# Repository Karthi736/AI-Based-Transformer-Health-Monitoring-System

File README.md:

# Industrial Transformer Health Monitoring SCADA System

<div align="center">

</div>

---

---

An ESP32-based transformer health monitoring and preventive protection system with Firebase cloud communication and an industrial SCADA web dashboard.

## Project Overview

Transformer health monitoring is important for identifying abnormal operating conditions before they develop into serious faults.

This project demonstrates a smart monitoring and preventive protection approach using ESP32, DHT22, load simulation, relay protection, servo-based cooling, local LCD monitoring, Firebase cloud communication, and an industrial SCADA web dashboard.

The system continuously monitors transformer-related parameters and converts the collected information into an easy-to-understand health and risk status.

The overall monitoring workflow is:

**Sensors → ESP32 → Health Assessment → Risk Classification → Preventive Protection → Firebase → SCADA Dashboard**

---

## Key Features

- Real-time transformer condition monitoring
- Temperature monitoring
- Humidity monitoring
- Load percentage monitoring
- Transformer health score calculation
- LOW, MEDIUM, HIGH, and CRITICAL risk classification
- Automatic preventive protection
- Relay-based protection control
- Servo-based cooling control
- LED warning indication
- Buzzer alarm indication
- 16×2 I2C LCD monitoring
- ESP32-based processing
- Wi-Fi communication
- Firebase cloud communication
- Industrial SCADA web dashboard
- Remote transformer status monitoring
- Multi-transformer monitoring
- Separate simulation units for TR-001, TR-002, TR-003, and TR-004

---

## System Architecture

The complete system follows the architecture:

**DHT22 + Load Input → ESP32 → Health Assessment → Risk Classification → Preventive Protection → Firebase → SCADA Dashboard**

---

## Documentation

### System Architecture

<div align="center">

</div>

### Block Diagram

<div align="center">

</div>

### Flowchart

<div align="center">

</div>

### Circuit Diagram

<div align="center">

</div>

---

## Hardware Components

| Component | Function |
|---|---|
| ESP32 | Main controller, data processing, Wi-Fi and Firebase communication |
| DHT22 | Temperature and humidity monitoring |
| Potentiometer | Transformer load percentage simulation |
| 16×2 I2C LCD | Local transformer monitoring and status display |
| Relay Module | Preventive protection control |
| Servo Motor | Automatic cooling mechanism |
| LED | Visual warning indication |
| Buzzer | Audible alarm indication |

---

## Hardware Functions

### ESP32

The ESP32 acts as the central controller of the system. It collects sensor values, processes transformer operating parameters, calculates the health score, determines the risk level, controls protection devices, and communicates monitoring data to Firebase through Wi-Fi.

### DHT22

The DHT22 sensor provides temperature and humidity measurements used for transformer condition monitoring.

### Potentiometer

The potentiometer is used as a simulated load input. Its value represents the transformer load percentage during the simulation.

### 16×2 I2C LCD

The LCD provides local monitoring of important transformer parameters and operating status.

### Relay Module

The relay provides a control mechanism for preventive protection during critical transformer conditions.

### Servo Motor

The servo motor represents an automatic cooling mechanism that operates according to the transformer risk condition.

### LED

The LED provides a visual warning indication when abnormal or critical conditions are detected.

### Buzzer

The buzzer provides an audible alarm during abnormal and critical operating conditions.

---

## Technologies Used

- ESP32
- Arduino IDE
- DHT22
- 16×2 I2C LCD
- Potentiometer
- Relay Module
- Servo Motor
- LED
- Buzzer
- Wi-Fi
- Firebase
- HTML
- CSS
- JavaScript
- SCADA Web Dashboard
- Wokwi Simulation

---

## Monitoring Parameters

The system monitors the following parameters:

| Parameter | Source | Purpose |
|---|---|---|
| Temperature | DHT22 | Transformer thermal condition |
| Humidity | DHT22 | Environmental monitoring |
| Load Percentage | Potentiometer | Transformer load simulation |
| Health Score | ESP32 | Overall transformer condition |
| Risk Level | ESP32 | Transformer condition classification |
| Relay Status | ESP32 | Preventive protection status |
| Cooling Status | Servo | Cooling mechanism status |
| Alarm Status | LED + Buzzer | Warning and critical indication |
| Fault Count | ESP32 | Critical fault tracking |
| Transformer Status | ESP32 / Firebase | Overall operating condition |

---

## Health and Risk Classification

The transformer condition is classified using the calculated health score.

| Health Score | Risk Level | System Response |
|---|---|---|
| 80–100 | LOW | Normal Monitoring |
| 50–79 | MEDIUM | Warning Monitoring |
| 25–49 | HIGH | Preventive Action |
| Below 25 | CRITICAL | Protection Activated |

The health score provides a simplified representation of the transformer operating condition and allows the system to classify the current risk level.

---

## Preventive Protection

The system is designed to respond automatically when a critical transformer condition is detected.

During a critical condition:

- Relay protection is activated.
- Servo-based cooling is activated.
- LED warning indication is enabled.
- Buzzer alarm is activated.
- LCD status is updated.
- Transformer status is updated in Firebase.
- SCADA dashboard displays the updated protection condition.

This provides an automated preventive response instead of relying only on manual monitoring.

---

## Firebase Cloud Communication

The ESP32 communicates with Firebase using Wi-Fi.

Firebase acts as the cloud data layer between the ESP32 monitoring system and the SCADA web dashboard.

The monitoring data transmitted to Firebase can include:

- Temperature
- Humidity
- Load Percentage
- Health Score
- Risk Level
- Relay Status
- Cooling Status
- Alarm Status
- Fault Count
- Transformer Status

The SCADA dashboard uses the Firebase data to provide centralized remote monitoring.

---

## SCADA Web Dashboard

The industrial SCADA web dashboard provides a centralized interface for monitoring transformer operating conditions.

The dashboard can display:

- Real-time Temperature
- Humidity
- Load Percentage
- Health Score
- Risk Level
- Relay Status
- Cooling Status
- Alarm Status
- Fault Count
- Transformer Status

The dashboard is designed to provide a clear view of transformer health and protection status.

The multi-transformer configuration allows separate transformer units to be monitored from a centralized SCADA interface.

---

## Multi-Transformer Simulation

The project includes four separate transformer simulation units.

### TR-001

[View TR-001 Wokwi Simulation](https://wokwi.com/projects/472072364712871937)

### TR-002

[View TR-002 Wokwi Simulation](https://wokwi.com/projects/471997864432481281)

### TR-003

[View TR-003 Wokwi Simulation](https://wokwi.com/projects/471997923499829249)

### TR-004

[View TR-004 Wokwi Simulation](https://wokwi.com/projects/471997982880700417)

These simulation units demonstrate the monitoring concept for multiple transformer units.

---

## Simulation Conditions

The system can be evaluated under different operating conditions by changing the temperature and load inputs.

### Normal Condition

Under normal operating conditions:

- Health score remains high.
- Risk level remains LOW.
- Relay protection remains inactive.
- Cooling remains inactive.
- Alarm indication remains OFF.
- Transformer status remains normal.

### Warning Condition

When temperature or load increases:

- Health score decreases.
- Risk level changes to MEDIUM or HIGH depending on the calculated condition.
- Warning indication is generated.
- LCD displays the updated condition.
- Monitoring information is updated in the cloud dashboard.

### Critical Condition

When the transformer operating condition reaches a critical level:

- Risk level becomes CRITICAL.
- Relay protection is activated.
- Servo cooling is activated.
- LED warning is activated.
- Buzzer alarm is activated.
- Firebase data is updated.
- SCADA dashboard displays the critical transformer condition.
---
## Advantages

- Continuous transformer condition monitoring
- Real-time temperature and humidity monitoring
- Load condition monitoring
- Automatic transformer health assessment
- Automatic risk classification
- Preventive protection response
- Automatic cooling control
- Local LCD monitoring
- LED and buzzer warning indication
- Firebase cloud communication
- Remote SCADA monitoring
- Centralized multi-transformer monitoring
- Real-time transformer status visualization
- Expandable monitoring architecture
- Suitable as a prototype for smart transformer monitoring applications

---

## Future Scope

The system can be further developed by integrating additional transformer parameters and advanced monitoring technologies.

- Transformer oil temperature monitoring
- Transformer oil level monitoring
- Transformer current and voltage monitoring
- Transformer vibration monitoring
- Power factor monitoring
- Energy monitoring
- Historical transformer data analysis
- Real-time trend analysis
- Advanced predictive maintenance algorithms
- Machine learning-based fault prediction
- Automated fault classification
- Mobile monitoring application
- Large-scale multi-transformer SCADA deployment
- Industrial communication protocol integration
- Advanced alarm and event management
- Remote diagnostic support

---

## Conclusion

The Industrial Transformer Health Monitoring SCADA System demonstrates an integrated approach to transformer condition monitoring and preventive protection using ESP32, sensors, protection devices, Firebase cloud communication, and an industrial SCADA web dashboard.

The ESP32 collects transformer operating parameters and processes the collected information to determine the transformer health condition and risk level. Based on the detected condition, the system provides warning indications and automatically activates preventive protection during critical operating conditions.

Firebase provides the cloud communication layer, while the SCADA web dashboard provides centralized remote visualization of transformer operating parameters and protection status.

The multi-transformer simulation using TR-001, TR-002, TR-003, and TR-004 demonstrates the possibility of extending the system to multiple transformer monitoring units.

The complete system workflow is:

**Sensors → ESP32 → Health Assessment → Risk Classification → Preventive Protection → Firebase → SCADA Dashboard**

---

## Author

**Karthikeyan M**

B.E. Electrical and Electronics Engineering  
V.S.B College of Engineering Technical Campus  
2023–2027

---
## Project Structure

```text
AI-Based-Transformer-Health-Monitoring-System/
│
├── Arduino_Code/
│   └── Smart_Transformer_Health_Monitoring.ino
│
├── Dashboard/
│   ├── index.html
│   ├── style.css
│   └── script.js
│
├── Documentation/
│   ├── Block_Diagram.png
│   ├── Circuit_Diagram.png
│   ├── Flowchart.png
│   ├── System_Architecture.png
│   └── Simulation_Details.md
│
├── Images/
│   ├── Block_Diagram.png
│   ├── Circuit_Diagram.png
│   ├── Flowchart.png
│   └── System_Architecture.png
│
├── Simulation/
│   ├── TR-001
│   ├── TR-002
│   ├── TR-003
│   └── TR-004
│
├── simulator/
│   └── firebase-config.js
│
├── README.md
└── LICENSE

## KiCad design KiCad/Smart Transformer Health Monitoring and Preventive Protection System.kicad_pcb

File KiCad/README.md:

# KiCad Files

This folder contains the KiCad project files including the schematic, PCB layout, and 3D PCB design.

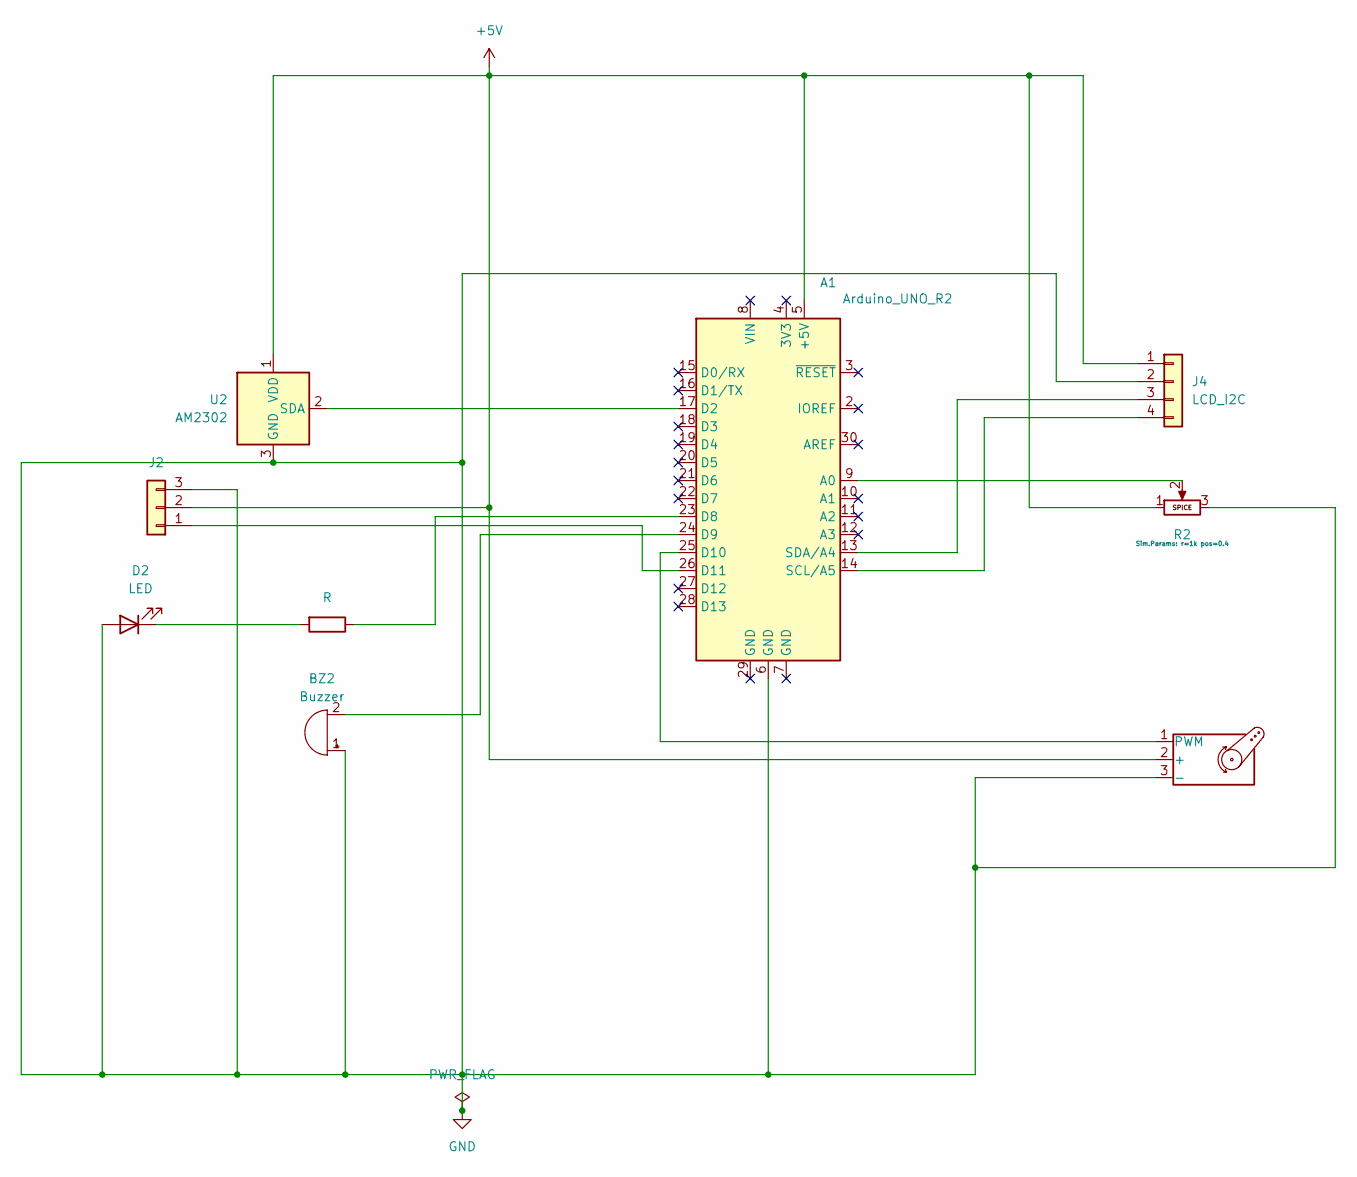
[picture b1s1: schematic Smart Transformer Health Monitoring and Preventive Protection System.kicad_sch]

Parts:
A1: Arduino_UNO_R2
BZ2: Buzzer; LED_D5.0mm
D2: LED; LED_D5.0mm
J2: Relay Module; FanPinHeader_1x03_P2.54mm_Vertical
J4: LCD_I2C; FanPinHeader_1x04_P2.54mm_Vertical
M2: Motor_Servo; FanPinHeader_1x03_P2.54mm_Vertical
R1: R; R_Axial_DIN0207_L6.3mm_D2.5mm_P7.62mm_Horizontal
R2: Potentiometer; PinHeader_1x03_P2.54mm_Vertical
U2: AM2302; ASAIR_AM2302_P2.54mm_Vertical

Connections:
+5V: A1.5 (+5V), J2.2, J4.1, M2.2 (+), R2.1, U2.1 (VDD)
GND: A1.6 (GND), BZ2.1 (+), D2.2 (A), J2.3, J4.2, M2.3 (-), R2.3, U2.3 (GND), U2.4 (GND)
unnamed: A1.9 (A0), R2.2
unnamed: A1.17 (D2), U2.2 (SDA)
unnamed: A1.23 (D8), R1.1
unnamed: A1.24 (D9), BZ2.2 (-)
unnamed: A1.25 (D10), M2.1 (PWM)
unnamed: A1.26 (D11), J2.1
unnamed: A1.14 (SCL/A5), J4.4
unnamed: A1.13 (SDA/A4), J4.3
unnamed: D2.1 (K), R1.2

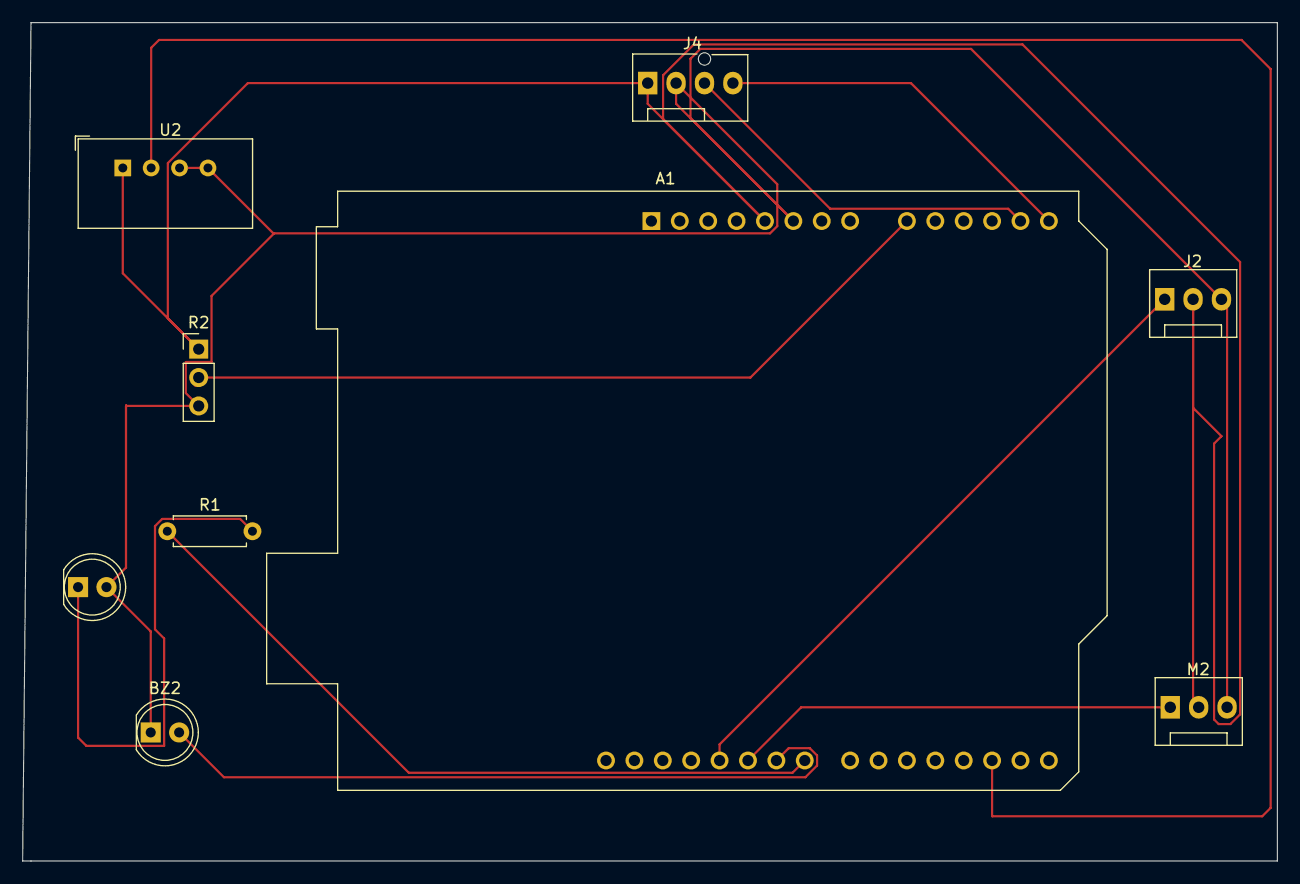
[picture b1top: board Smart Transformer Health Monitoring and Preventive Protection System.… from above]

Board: 2 copper layers, 112.3 x 75.0 mm, 9 parts (0 on the bottom side), 11 nets.

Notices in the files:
README.md:
License: MIT
